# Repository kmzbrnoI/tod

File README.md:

TOD – DCC Track Occupancy Detector
==================================

TOD is a DCC-only track occupancy detector for model railroad.

Basic features:
* Up 4 tracks
* Galvanically separated outputs
* Section occupied = output grounded
* No special power supply required
* Maximum track current: 3 A continuous without passive cooler,
  5 A continuous with passive cooler.
* Could be divided into pairs with separated J&K
* Easily automatically-mounted-parts via JlcPcb

This repository contains schematics & PCB layout of TOD PCB.

## Design

Schematics & PCB are designed in KiCad 8.

## Production

PCB is prepared to be automatically assembled in [JLCPCB](https://jlcpcb.com/).
SMD parts on **bottom** side should be assembled. Each SMD part has its `LCSC_ITEM`
attribute set.

```bash
$ make fab
```

## Authors

TOD is designed by [Model Railroaders Club
Brno](https://www.kmz-brno.cz/), [Jan Horáček](mailto:jan.horacek@kmz-brno.cz).
Inspiration from Vladimíř Soukup, Zababov.

## License

Content of the repository is provided under [Creative Commons
Attribution-ShareAlike 4.0
License](https://creativecommons.org/licenses/by-sa/4.0/) as openhardware
project. You may download any data, contribute to the project, create PCB
yourself or even sell it yourself.

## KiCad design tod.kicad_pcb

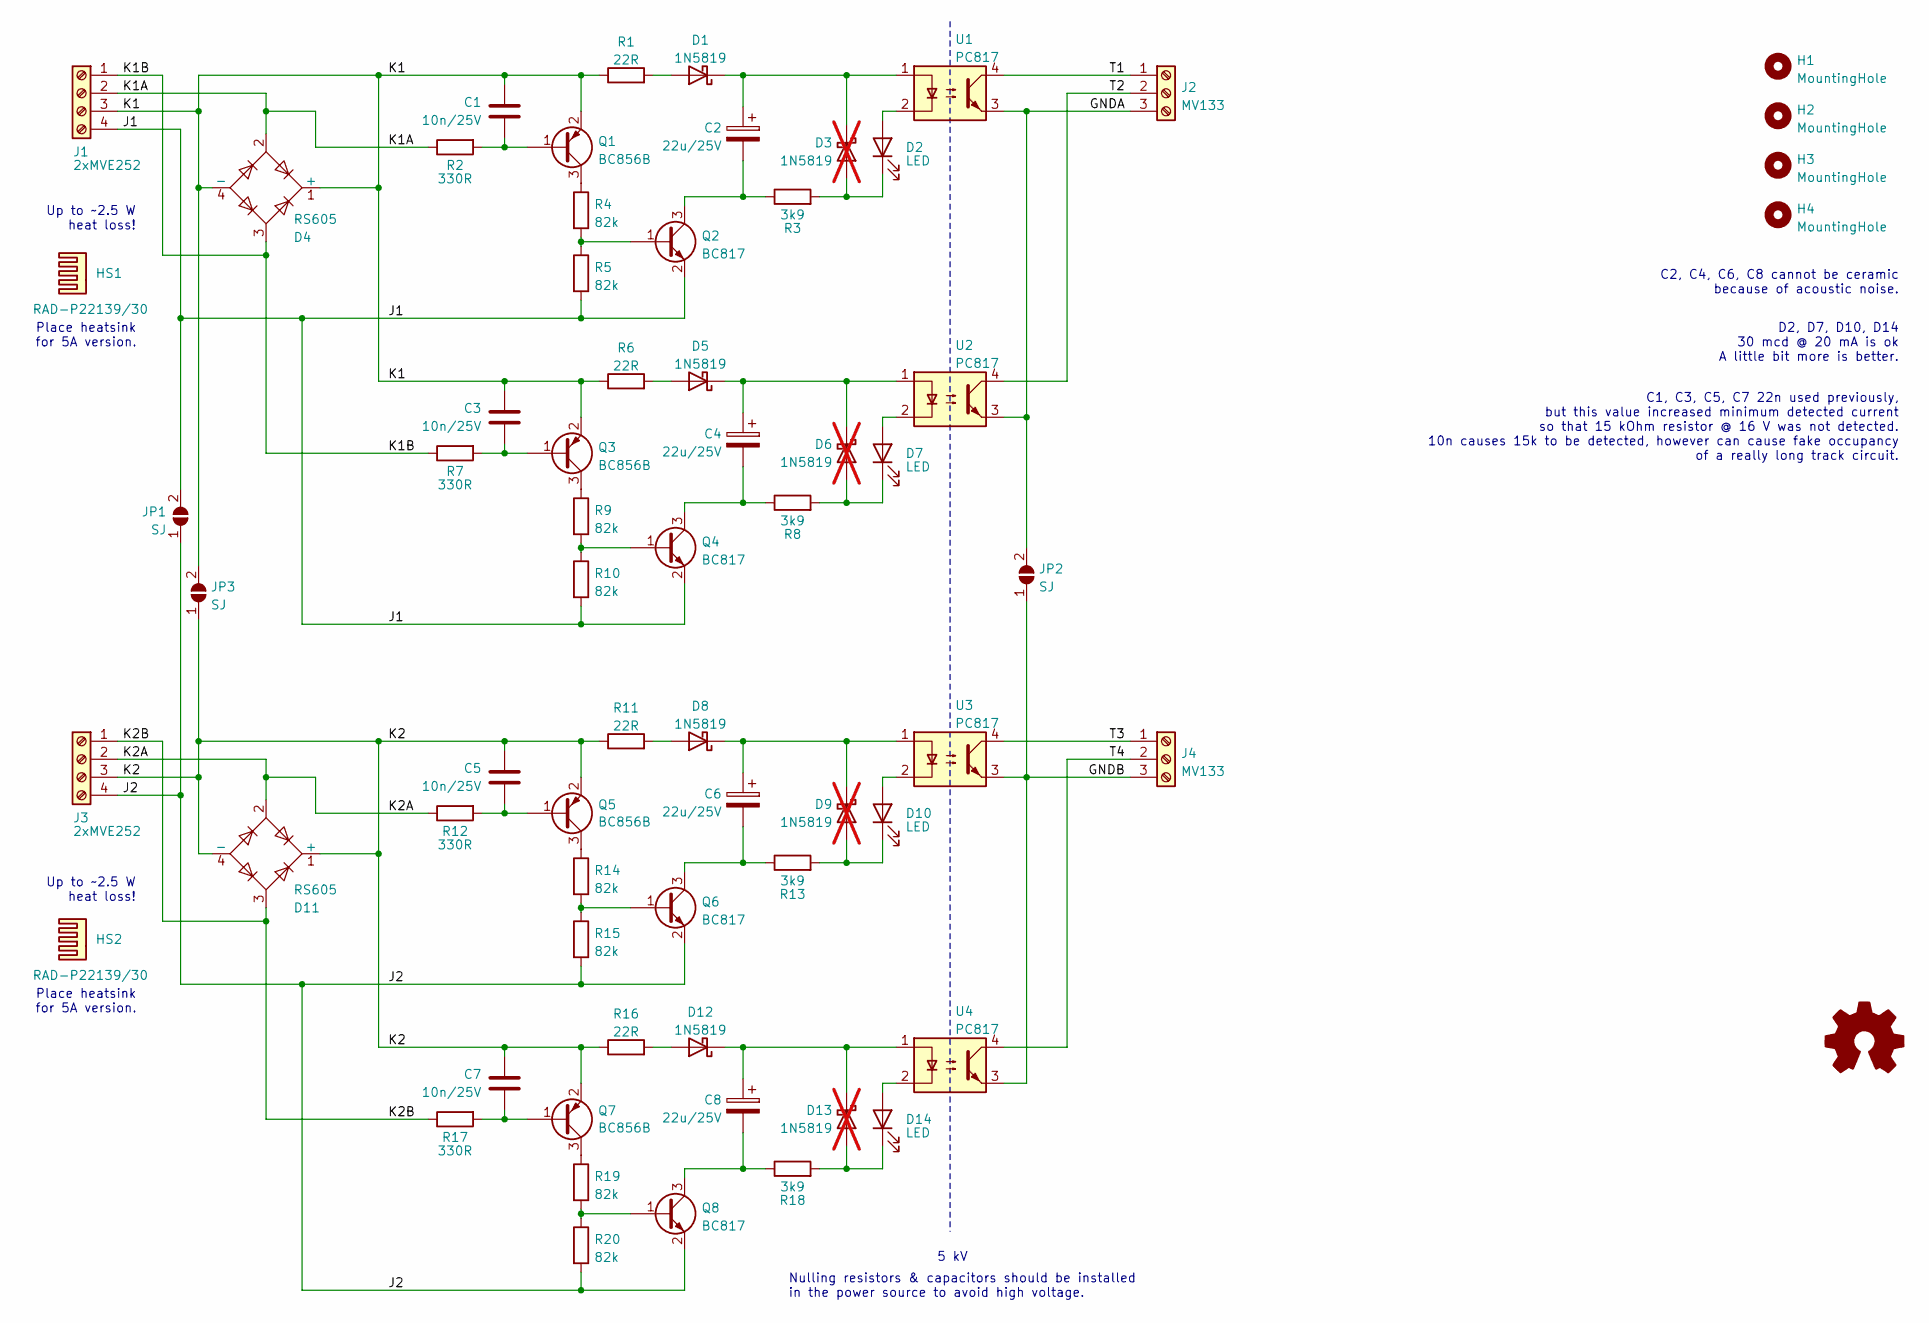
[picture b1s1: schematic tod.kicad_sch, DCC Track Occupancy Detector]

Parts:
C1, C3, C5, C7: 10n/25V; C_0805_2012Metric_Pad1.18x1.45mm_HandSolder; LCSC C1710
C2, C4, C6, C8: 22u/25V; CP_Radial_D5.0mm_P2.00mm; JLCPCB_IGNORE true
D1, D5, D8, D12: 1N5819; D_SOD-323_HandSoldering; LCSC C191023
D2, D7, D10, D14: LED; LED_D3.0mm
D3, D6, D9, D13: 1N5819; D_SOD-323_HandSoldering; LCSC C191023; not fitted
D4, D11: RS605; Diode_Bridge_Vishay_GBU
H1, H2, H3, H4: MountingHole; MountingHole_3.2mm_M3_Pad
HS1, HS2: RAD-P22139/30
J1, J3: 2xMVE252; MVE252-5-V-2x
J2, J4: MV133; TerminalBlock_4Ucon_1x03_P3.50mm_Horizontal
JP1, JP2, JP3: SJ; SolderJumper-2_P1.3mm_Open_RoundedPad1.0x1.5mm
Q1, Q3, Q5, Q7: BC856B; SOT-23; LCSC C2149
Q2, Q4, Q6, Q8: BC817; SOT-23; LCSC C2150
R1, R6, R11, R16: 22R; R_0805_2012Metric_Pad1.20x1.40mm_HandSolder; LCSC C17561
R2, R7, R12, R17: 330R; R_0805_2012Metric_Pad1.20x1.40mm_HandSolder; LCSC C17630
R3, R8, R13, R18: 3k9; R_0805_2012Metric_Pad1.20x1.40mm_HandSolder; LCSC C17614
R4, R5, R9, R10, R14, R15, R19, R20: 82k; R_0805_2012Metric_Pad1.20x1.40mm_HandSolder; LCSC C17840
U1, U2, U3, U4: PC817; DIP-4_W7.62mm_LongPads

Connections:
/GNDA: J2.3, JP2.2 (B), U1.3, U2.3
/GNDB: J4.3, JP2.1 (A), U3.3, U4.3
/J1: J1.4, JP1.2 (B), Q2.2 (E), Q4.2 (E), R5.2, R10.2
/J2: J3.4, JP1.1 (A), Q6.2 (E), Q8.2 (E), R15.2, R20.2
/K1: C1.1, C3.1, D4.1 (+), D4.4 (-), J1.3, JP3.2 (B), Q1.2 (E), Q3.2 (E), R1.1, R6.1
/K1A: D4.2, J1.2, R2.1
/K1B: D4.3, J1.1, R7.1
/K2: C5.1, C7.1, D11.1 (+), D11.4 (-), J3.3, JP3.1 (A), Q5.2 (E), Q7.2 (E), R11.1, R16.1
/K2A: D11.2, J3.2, R12.1
/K2B: D11.3, J3.1, R17.1
/T1: J2.1, U1.4
/T2: J2.2, U2.4
/T3: J4.1, U3.4
/T4: J4.2, U4.4
unnamed: D1.2 (A), R1.2
unnamed: C2.1, D1.1 (K), D3.1 (K), U1.1
unnamed: D2.2 (A), U1.2
unnamed: D2.1 (K), D3.2 (A), R3.2
unnamed: D5.2 (A), R6.2
unnamed: C4.1, D5.1 (K), D6.1 (K), U2.1
unnamed: D6.2 (A), D7.1 (K), R8.2
unnamed: D7.2 (A), U2.2
unnamed: D8.2 (A), R11.2
unnamed: C6.1, D8.1 (K), D9.1 (K), U3.1
unnamed: D10.2 (A), U3.2
unnamed: D9.2 (A), D10.1 (K), R13.2
unnamed: D12.2 (A), R16.2
unnamed: C8.1, D12.1 (K), D13.1 (K), U4.1
unnamed: D13.2 (A), D14.1 (K), R18.2
unnamed: D14.2 (A), U4.2
unnamed: C1.2, Q1.1 (B), R2.2
unnamed: Q1.3 (C), R4.1
unnamed: Q2.1 (B), R4.2, R5.1
unnamed: C2.2, Q2.3 (C), R3.1
unnamed: C3.2, Q3.1 (B), R7.2
unnamed: Q3.3 (C), R9.1
unnamed: Q4.1 (B), R9.2, R10.1
unnamed: C4.2, Q4.3 (C), R8.1
unnamed: C5.2, Q5.1 (B), R12.2
unnamed: Q5.3 (C), R14.1
unnamed: Q6.1 (B), R14.2, R15.1
unnamed: C6.2, Q6.3 (C), R13.1
unnamed: C7.2, Q7.1 (B), R17.2
unnamed: Q7.3 (C), R19.1
unnamed: Q8.1 (B), R19.2, R20.1
unnamed: C8.2, Q8.3 (C), R18.1

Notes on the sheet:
C1, C3, C5, C7 22n used previously, but this value increased minimum detected current so that 15 kOhm resistor @ 16 V was not detected. 10n causes 15k to be detected, however can cause fake occupancy of a really long track circuit.
Place heatsink for 5A version.
Up to ~2.5 W heat loss!
5 kV
Nulling resistors & capacitors should be installed in the power source to avoid high voltage.
D2, D7, D10, D14 30 mcd @ 20 mA is ok A little bit more is better.
C2, C4, C6, C8 cannot be ceramic because of acoustic noise.

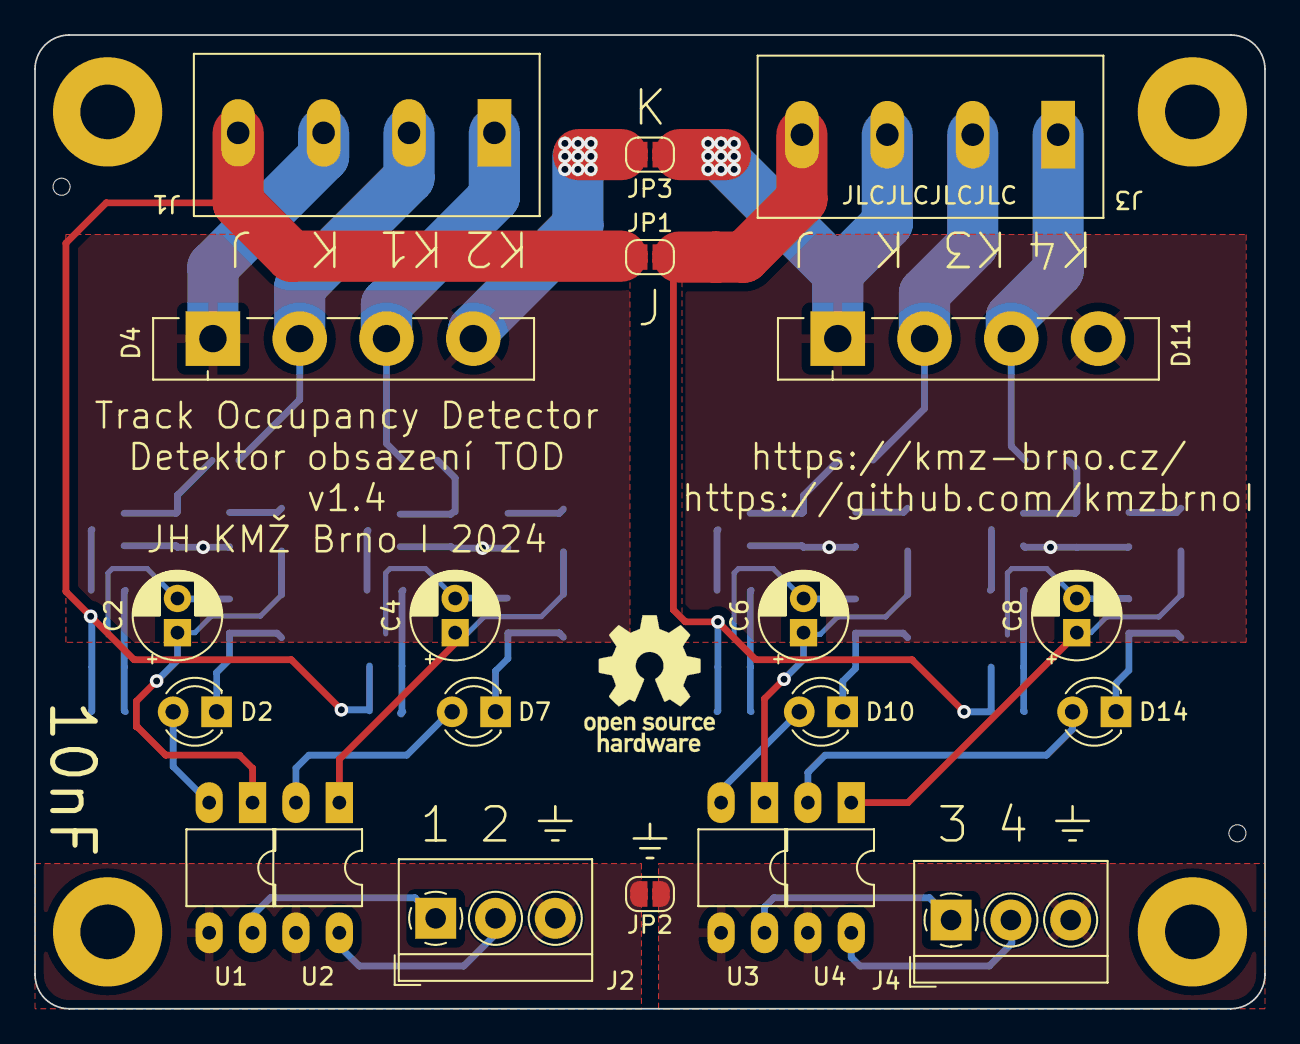
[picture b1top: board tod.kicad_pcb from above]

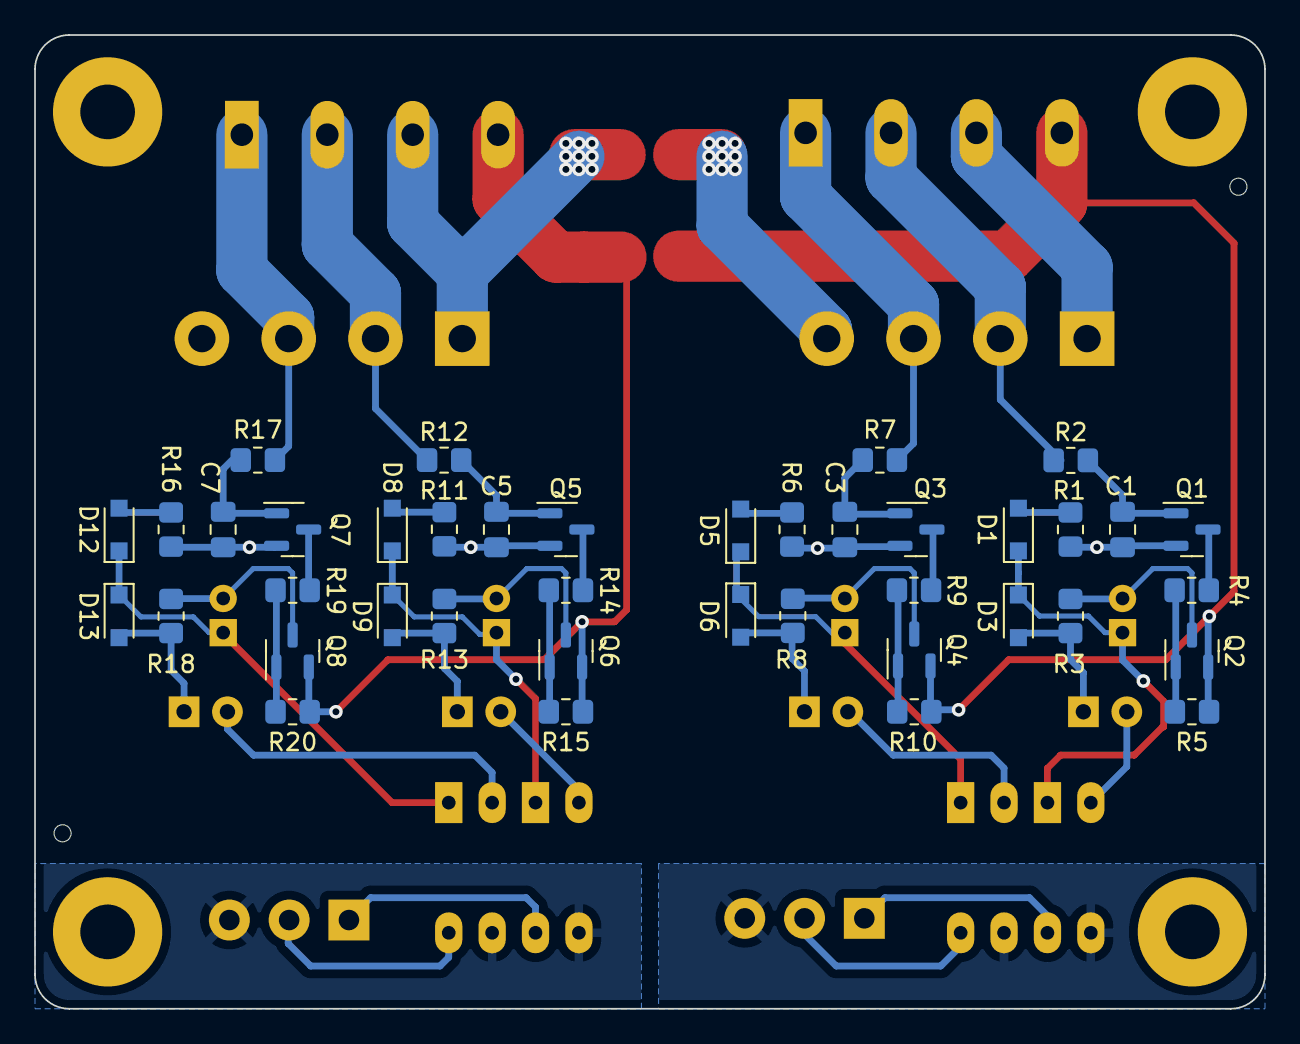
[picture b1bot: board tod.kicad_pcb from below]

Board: 2 copper layers, 72.0 x 57.0 mm, 65 parts (40 on the bottom side), 46 nets.

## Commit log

2022-07-19 Add KiCad .gitignore.
2022-07-19 Add empty KiCad project.
2022-07-19 Add first half-detector.
2022-07-21 Add rest of schematics.
2022-07-21 Add footprints & LCSC numbers.
2022-07-25 Add protective diodes (probably won't be fitted).
2022-07-25 Make solderjumpers open by default.
    They will be closed by soldering when manufacturing.
    Reasor: it's much easier to unsolder on mounted PCB than to cut PCB
    to disconnect.
2022-07-25 Add not about isolation resistors & capacitors.
2022-07-25 Minor schematic tweaks.
2022-08-15 Route PCB.
2022-08-15 Tweak silkscreen.
2022-08-18 Add proper MVE252-5-V footprints.
2022-08-18 Add mountholes.
2022-08-18 Add kikit fab process.
2022-08-18 Add JLCPCB_CORRECTION where required.
2022-08-18 LCSC: use cheaper transistors than BC817.
2022-08-18 Wire unrouted paths.
2022-08-18 Resolve DRC issues.
2022-08-18 Use cheaper transistors.
2022-08-18 Do not place non-necessarry diodes.
2022-09-01 Minor silkscreen tweaks.
2022-10-05 Add heat loss notice.
2022-10-05 Add CC license.
2022-10-05 Add README.
2022-10-05 Increase round corners diameter.
2022-10-05 Add heatplanes.
2022-10-05 Add silkscreen texts & logos.
2022-10-05 Add JLCJLCJLCJLC text for manufacturing id.
2022-10-08 Use 2k resistors instead of 3k9.
2022-10-08 Really do not fit unused diodes.
2022-10-09 Revert "Use 2k resistors instead of 3k9."
    This reverts commit e4b48c20f046feec0504172c1823d5e465362b53.
2022-10-10 Add proper README.
2022-10-10 Add license.
2022-10-21 Note max current with cooler.
2023-03-15 Add capacitor value to silkscreen.
2023-03-15 Use screw terminals schematics mark insted of generic connector.
2023-03-15 Fix inconsistent text.
2023-03-15 Add proper part values to screw terminals.
2023-03-15 Use new LCSC number for 22uF 0805 capacitors.
2023-04-20 Use electrolytic capacitors for 22uF C.
2023-04-20 New capacitors: add JLCPCB_IGNORE.
2023-12-05 Migrate to KiCad 7, add missing 'B' to all BC856 transistors.
2023-12-05 Use DNP where appropriate.
2023-12-27 Add note regarding LEDs brightness.
2024-02-23 22n -> 10n damping capacitors.
2024-12-08 Migrate to KiCad 8.
2024-12-08 Use specific GBU8D-DC.
    GBU8M-DIO does not work - it has higher forward voltage.
2024-12-08 Sch: add optional heatsinks.
2024-12-13 Add capacitor's voltage.
2024-12-15 Use RS605 bridges.

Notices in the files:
tod.kicad_sch:
Released under the Creative Commons Attribution-ShareAlike 4.0 License
